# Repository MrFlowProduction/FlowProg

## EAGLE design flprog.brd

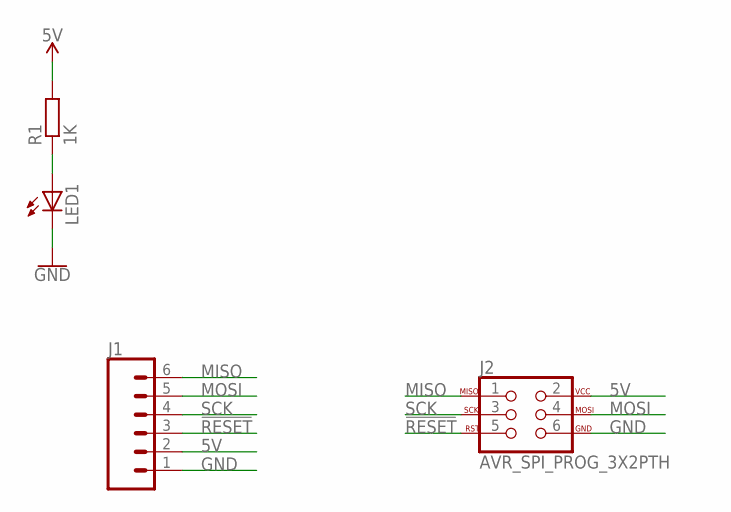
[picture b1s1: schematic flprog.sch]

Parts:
J1: CONN_06SMD-1MM; 1X06-1MM
J2: AVR_SPI_PROG_3X2PTH; 2X3
LED1: LEDCHIPLED_0603; CHIPLED_0603
R1: 1K; R0603

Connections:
5V: J1.2, J2.2, R1.2
!RESET: J1.3, J2.5
GND: J1.1, J2.6, LED1.C
MISO: J1.6, J2.1
MOSI: J1.5, J2.4
unnamed: LED1.A, R1.1
SCK: J1.4, J2.3

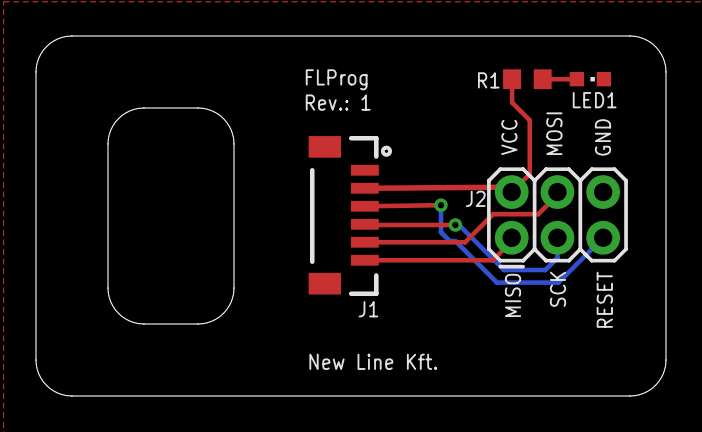
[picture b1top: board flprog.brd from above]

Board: 2 copper layers, 35.0 x 20.0 mm, 4 parts (0 on the bottom side), 7 nets.

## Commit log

2021-05-21 First Commit
    Base Board
2021-06-11 gerbers
2022-02-17 FPC fix

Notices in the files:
parts and their libraries:
SparkFun-Connectors: Licensing: Creative Commons ShareAlike 4.0 International - https://creativecommons.org/licenses/by-sa/4.0
